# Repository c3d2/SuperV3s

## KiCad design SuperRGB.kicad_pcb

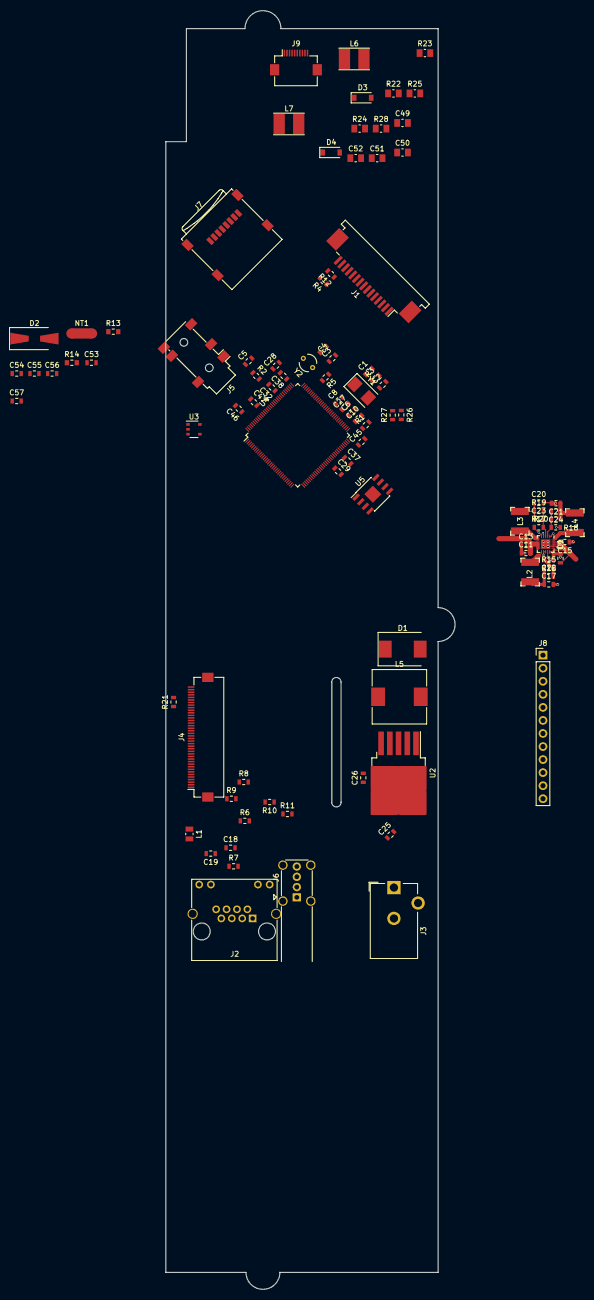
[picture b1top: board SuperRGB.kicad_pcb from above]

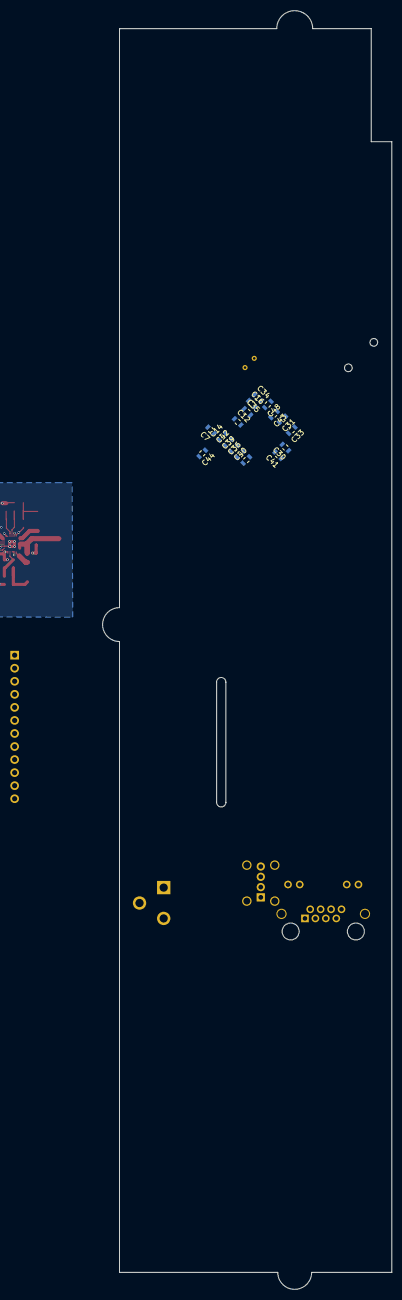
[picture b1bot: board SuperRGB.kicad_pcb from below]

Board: 2 copper layers, 56.3 x 248.9 mm, 113 parts (17 on the bottom side), 100 nets.

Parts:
C1, C2, C3, C4: 18p; C_0603_1608Metric
C5: 1n; C_0603_1608Metric
C6, C11, C13, C15, C17, C20, C21, C29, C46: 10u; C_0603_1608Metric
C7, C12, C14, C16, C18, C19, C30, C31, C32, C33, C34, C35, C36, C37, C38, C39, C40, C41, C42, C43, C44, C45, C47, C48: 100n; C_0603_1608Metric
C8, C9, C10, C27, C28, C53: 1u; C_0603_1608Metric
C22, C23, C24: 220p; C_0603_1608Metric
C25, C26: 22u; C_0603_1608Metric
C49, C50, C52: 4u7; C_0805_2012Metric_Pad1.15x1.50mm_HandSolder
C51: 1u; C_0805_2012Metric_Pad1.15x1.50mm_HandSolder
C54: 1p; C_0603_1608Metric
C55: 1p2; C_0603_1608Metric
C56: 10p; C_0603_1608Metric
C57: 2n7; C_0603_1608Metric
D1: B340A; D_SMC
D2: SS34; D_SMA-SMB_Universal_Handsoldering
D3, D4: SB120; D_SOD-123
J1: Conn_01x15; TE_1-84953-5_1x15_P1.0mm_Horizontal
J2: RJ45-TRANSFO; RJ45_Amphenol_RJHSE538X
J3: Barrel_Jack; BarrelJack_CUI_PJ-102AH_Horizontal
J4: Conn_01x40; Hirose_FH12-40S-0.5SH_1x40_P0.50mm_Horizontal
J5: Audio-Jack-4; Jack_3.5mm_PJ311_Horizontal
J6: USB_A; USB_A_Horizontal_Upright
J7: Micro_SD_Card; microSD_HC_Wuerth_693072010801
J8: Conn_01x12_Male; PinHeader_1x12_P2.54mm_Vertical
J9: Conn_01x10; Hirose_FH12-10S-0.5SH_1x10_P0.50mm_Horizontal
L1: 10u; L_0805_2012Metric
L2, L3, L4: 1u; L_CD32_3.5x3.0_H2.1
L5: 47u; L_10.4x10.4_H4.8
L6, L7: L_Core_Ferrite; L_Taiyo-Yuden_NR-40xx_HandSoldering
NT1: Net-Tie_2; NetTie-2_SMD_Pad2.0mm
R1: 240; R_0603_1608Metric
R2: 47k; R_0603_1608Metric
R3: 10M; R_0603_1608Metric
R4, R12: 2k2; R_0603_1608Metric
R5: 6k; R_0603_1608Metric
R6, R7, R8, R9: 51; R_0603_1608Metric
R10, R11: 1k; R_0603_1608Metric
R13, R14: 100k; R_0603_1608Metric_Pad0.84x1.00mm_HandSolder
R15, R16, R17: 100k; R_0603_1608Metric
R18: 110k; R_0603_1608Metric
R19: 150k; R_0603_1608Metric
R20: 510k; R_0603_1608Metric
R21: 10k; R_0603_1608Metric
R22: 0.68; R_0805_2012Metric_Pad1.15x1.50mm_HandSolder
R23, R24, R25: 1; R_0805_2012Metric_Pad1.15x1.50mm_HandSolder
R26, R27: 2k; R_0603_1608Metric
R28: 6.18; R_0805_2012Metric_Pad1.15x1.50mm_HandSolder
U1: EA3036; UQFN-20-1EP_3x3mm_P0.4mm
U2: AP1501; TO-263-5_TabPin3
U3: NCP114SN; TSOP-5_1.65x3.05mm_P0.95mm
U4: V3S_QFP-128; LQFP-128_14x14mm_P0.4mm
U5: GD5F1GQ4UAYIG; SOIC-8-1EP_3.9x4.9mm_P1.27mm
Y1: 24MHz; Crystal_SMD_5032-2Pin_5.0x3.2mm
Y2: 32768; Crystal_AT310_D3.0mm_L10.0mm_Vertical

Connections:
+1V2: C16.1, C21.1, C24.1, C39.1, C40.1, C41.1, C42.1, C43.1, L4.2, R20.1, U4.19, U4.20, U4.21, U4.25, U4.26, U4.38, U4.47, U4.51, U4.56, U4.58, U4.64, U4.80, U4.88, U4.108, U4.126
+1V8: C6.1, C8.1, C10.1, C12.1, C14.1, C20.1, C23.1, C44.1, L3.2, R19.1, R26.1, U4.59, U4.60, U4.61, U4.62, U4.65, U4.66, U4.67, U4.68, U4.69, U4.70, U4.72, U4.79
+3V0: C27.1, C31.1, C33.1, U4.76, U4.115, U4.122
+3V3: C17.1, C22.1, C28.1, C29.1, C30.1, C32.1, C34.1, C35.1, C36.1, C37.1, C38.1, C48.1, C53.1, J1.15, J4.36, J4.37, J4.38, J7.4, J8.12, L1.1, L2.2, R2.2, R4.2, R12.2, R13.1, R14.1, R15.1, R21.2, U4.12, U4.29, U4.50, U4.57, U4.85, U4.93, U4.98, U4.104, U4.109, U4.127, U5.3, U5.7, U5.8
+5V: C9.1, C11.2, C13.2, C15.2, C26.1, C50.1, C52.1, J6.1, L5.2, L6.1, L7.1, U1.7, U1.8, U1.9, U1.10, U1.16, U1.18, U1.19, U2.4, U3.1, U3.3
+12V: C25.1, D2.1, U2.1
/B0: J4.18, U4.33
/B1: J4.19, U4.32
/B2: J4.20, U4.31
/B3: J4.21, U4.30
/B4: J4.22, U4.28
/B5: J4.23, U4.27
/DCLK: J4.2, U4.37
/ENAB: J4.26, U4.36
/ETH_LINK_LED: R10.2, U4.77
/ETH_RXN: J2.6, R9.1, U4.89
/ETH_RXP: J2.4, R8.1, U4.90
/ETH_SPD_LED: R11.2, U4.78
/ETH_TXN: J2.3, R7.1, U4.91
/ETH_TXP: J2.1, R6.1, U4.92
/G0: J4.11, U4.24
/G1: J4.12, U4.23
/G2: J4.13, U4.22
/G3: J4.14, U4.18
/G4: J4.15, U4.17
/G5: J4.16, U4.16
/GPIO0: J8.11, U4.100
/HSYNC: J4.25, U4.35
/I2C0_SCL: J8.6, U4.45
/I2C0_SDA: J8.5, U4.46
/MCSI_CKN: J1.8, U4.87
/MCSI_CKP: J1.9, U4.86
/MCSI_D0N: J1.2, U4.82
/MCSI_D0P: J1.3, U4.81
/MCSI_D1N: J1.5, U4.84
/MCSI_D1P: J1.6, U4.83
/MCSI_SCL: J1.13, R12.1, U4.9
/MCSI_SDA: J1.14, R4.1, U4.8
/R0: J4.4, U4.15
/R1: J4.5, U4.14
/R2: J4.6, U4.13
/R3: J4.7, U4.11
/R4: J4.8, U4.7
/R5: J4.9, U4.6
/SDC0_CLK: J7.5, U4.105
/SDC0_CMD: J7.3, U4.103
/SDC0_D0: J7.7, U4.106
/SDC0_D1: J7.8, U4.107
/SDC0_D2: J7.1, U4.101
/SDC0_D3: J7.2, U4.102
/SPI_CS: U4.54, U5.1
/SPI_MISO: U4.52, U5.2
/SPI_MOSI: U4.55, U5.5
/SPI_SCK: U4.53, U5.6
/UART0_RX: J8.3, U4.49
/UART0_TX: J8.4, U4.48
/UART2_CTS: J8.7, U4.42
/UART2_RTS: J8.8, U4.41
/UART2_RX: J8.9, U4.40
/UART2_TX: J8.10, U4.39
/USB_DN: J6.2, U4.110
/USB_DP: J6.3, U4.111
/VSYNC: J4.27, U4.34
GND: C1.2, C2.2, C3.2, C4.2, C5.2, C6.2, C7.2, C8.2, C9.2, C10.2, C11.1, C12.2, C13.1, C14.2, C15.1, C16.2, C17.2, C18.2, C19.2, C20.2, C21.2, C25.2, C26.2, C28.2, C29.2, C30.2, C31.2, C32.2, C33.2, C34.2, C35.2, C36.2, C37.2, C38.2, C39.2, C40.2, C41.2, C42.2, C43.2, C45.2, C48.2, C49.2, C50.2, C51.2, C52.2, C53.2, C56.2, C57.1, D1.2, J1.1, J1.4, J1.7, J1.10, J2.8, J3.2, J3.3, J4.1, J4.3, J4.10, J4.17, J4.24, J4.28, J4.33, J4.34, J4.39, J4.40, J6.4, J6.5, J7.6, J7.9, J8.1, J8.2, NT1.2, R1.2, R5.1, R16.1, R17.1, R18.1, R22.2, R27.2, R28.2, U1.1, U1.4, U1.5, U1.12, U1.13, U1.15, U1.17, U1.21, U2.3, U2.5, U5.4
GNDA: C27.2, C46.2, C47.2, J5.4, NT1.1, U3.2, U4.116
unnamed: C1.1, R3.1, U4.75, Y1.1
unnamed: C2.1, R3.2, U4.74, Y1.2
unnamed: C3.1, U4.95, Y2.1
unnamed: C4.1, U4.96, Y2.2
unnamed: C5.1, R2.1, U4.112
unnamed: C7.1, U4.97
unnamed: C18.1, J2.2, L1.2, R6.2, R7.2
unnamed: C19.1, J2.5, R8.2, R9.2
unnamed: C22.2, R15.2, R16.2, U1.14
unnamed: C23.2, R17.2, R19.2, U1.3
unnamed: C24.2, R18.2, R20.2, U1.2
unnamed: C44.2, C45.1, R26.2, R27.1, U4.63, U4.71
unnamed: C46.1, C47.1, U4.123
unnamed: C54.1, C55.1, C57.2
unnamed: C54.2, C56.1
unnamed: D1.1, L5.1, U2.2
unnamed: D2.2, J3.1
unnamed: D3.2, L6.2
unnamed: D4.2, L7.2
unnamed: J4.29, J4.30, J4.31, J4.32, R21.1
unnamed: J5.1, U4.121
unnamed: J5.2, U4.120
unnamed: J9.4, R23.1
unnamed: J9.5, R24.1
unnamed: J9.6, R25.1
unnamed: L2.1, U1.11
unnamed: L3.1, U1.6
unnamed: L4.1, U1.20
unnamed: R1.1, U4.73
unnamed: R5.2, U4.94
unnamed: R13.2, R14.2
RLED_A: C51.1, D4.1, J9.3
RLED_K: J9.7, R28.1
WLED_A: C49.1, D3.1, J9.1, J9.2
WLED_K: R22.1, R23.2, R24.2, R25.2

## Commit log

2018-01-10 Schematic Part for MIC23450 Triple Step down converter
2018-01-12 bunch of custom symbols and footprints
2018-01-12 fix up project paths
2018-01-14 almost complete schematic, preliminary unrouted layout
2018-01-17 finished schematic for my V3s evaluation board
